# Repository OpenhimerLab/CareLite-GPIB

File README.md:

# CareLite-GPIB
CareLite is an open-source, tiny, small USB-GPIB adaptor based on STM32 with temperature sensors. 
It uses VCP (Virtual COM Port) and USB Type-C connector, without the need for external power; 
also with dedicated PC software (but not limited to), 
easy GPIB connection can be established and Prologix-like command protocol makes the compatiblity better, and real-time temp logging can be done by DS18B20 or so.

****I am NOT the author with no any relationship or benefit conflict with the author. I have no commercial intention to introdue this project and I have no intention to make benefits from this. 
All responsibility and risk or financial loss should be taken by the DIYers yourselves. The project is introduced and shared "AS IS".
Many functions, issues may exisit so use it at your own risk.

There are 2 version of MeterCare USB-GPIB converter, while sharing the same PC host Software, the firmware is unclear that both version could be applied.
We choose to introduce and share the "Lite" version firstly, as it is a simple, costless design somehow like AR488, 
but the designer reserves potentials to expand other functionality like temperature, humidity sensing ability (there is an UART+DS18B20 port, with proper firmware, it can be amazing for its various functionality!).

By the STM32F401, the CareLite can perform GPIB-USB conversion. 
In addition, there is a connector called MeterLink that provides the integration of multiple sensors(1 DS18B20 is confirmed to be functional).

Till now, at least 1 DS18B20 OneWire Temperature sensor can be used for logging temperature (by using MeterLink).

With the software written by "ZDD", you can connect a DMM and do a logging of both volt/ohm and temperature, and it will simutaneously calculate the math like temp.Co, or the deviation of logged data.
This makes it very clear to understand the dependency of multiple variables and its statistical property.

Also note that the software by ZDD is Labeview-based, you need to install:
1. NI Labview runtime
2. Local emulator to deal with encoding problems, as it is originally based on GBK simplified chinese, not UTF-8.

A sensor board with BMP180 and DS18B20, SHT2X is also possible for environment data logging, there is UART1 definition in MeterLink;
so it might be possible functional. This expansion board is mainly for the "Care" USB-GPIB, not sure if it is functional on CareLite.

The firmware is a bit messy, so try and find the best one for yourself. And explore the function, the Care ecosystem is very potential.
The protocol and communication is very like Prologix, using "++" command system, there are some explaination files, but it's in simplified Chinese,
for now I have no time to translate it, so please try by your own self. 
All in all, this is a tiny, easy to use GPIB adaptor for many devices, somthing like a STM32-based AR488 but with dedicated PC sotware!

For COPYright:

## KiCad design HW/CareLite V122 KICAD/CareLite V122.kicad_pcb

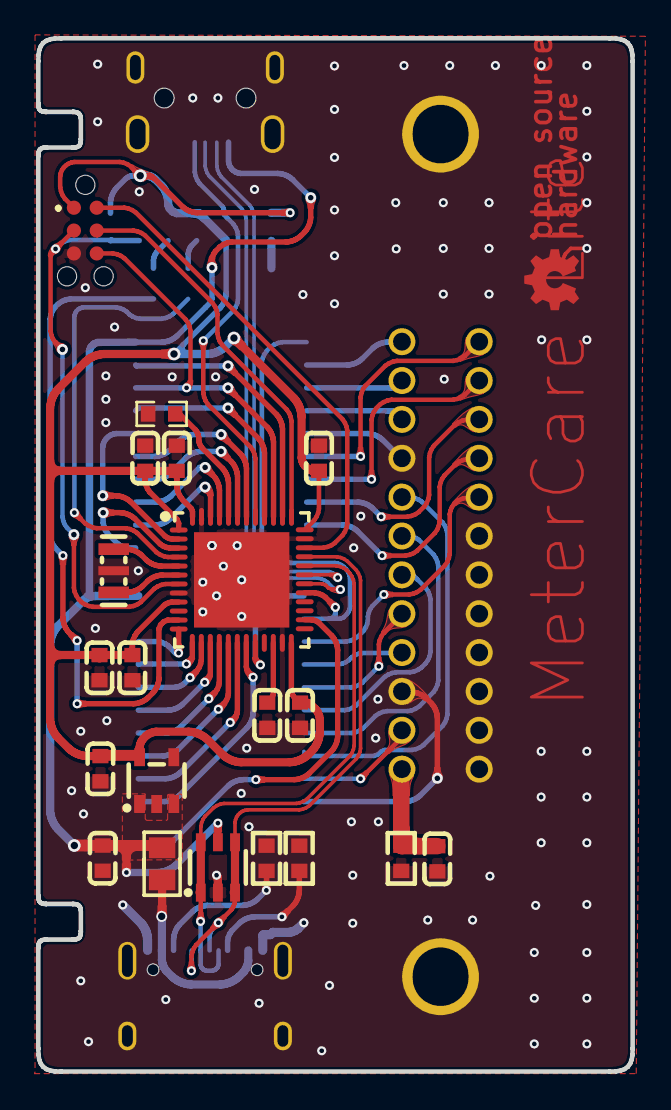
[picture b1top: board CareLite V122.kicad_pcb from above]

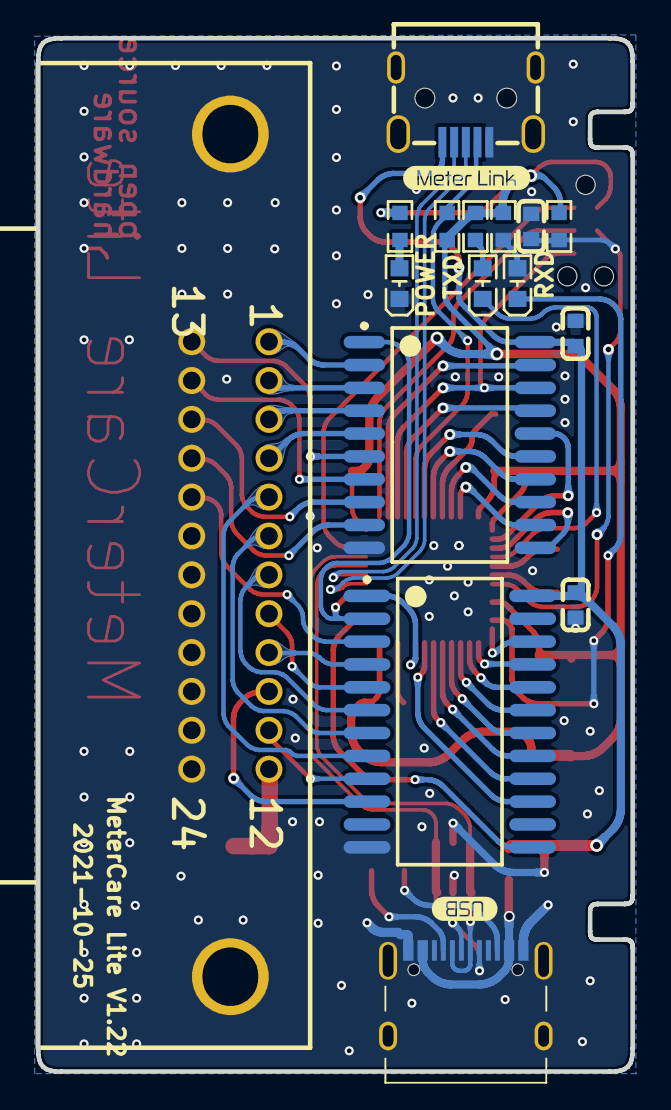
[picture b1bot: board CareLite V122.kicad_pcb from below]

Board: 2 copper layers, 33.0 x 57.4 mm, 37 parts (16 on the bottom side), 60 nets.

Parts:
C1, C12: 10uF; C0603
C2, C4, C6, C7, C8, C9, C10, C11: 100nF; C0603
C3: 4.7uF; C0603
C5: 1nF; C0603
C14: 100n; C0603
D1, D2, D3: LED; LED0603-FD
ESD: SRV05-4-P-T7; SOT-23-6_L2.9-W1.6-P0.95-LS2.8-BL
F1: 0.5A/6V; 0805_L_JX
GPIB: 112-024-113R001; IEEE-488 SOCKET, 24PIN, RIGHT ANGLE, MALE, 112-024-113R001,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
J1: 8.06.16; 80616-S
Pad_gge8544: Pad_gge8544
R1, R10: 5.1K; R0603
R2, R5, R6: 470R; R0603
R3, R9: 10K; R0603
R4: 1M; R0603
R7: 4.7K; R0603
U1: STM32F411CEU6TR; QFN-48_L7.0-W7.0-P0.50-BL-EP5.1
U2: LP5907QMFX-3.3Q1; SOT-23-5_L3.0-W1.7-P0.95-LS2.8-BR
U3: SN75160; SOIC127P1030-20AM
U5: SN75162; SOIC127P1030-24AM
USB: USB_C; USB_C_CUSB31-CFM2AX-01-Y
USB1: U-D-M7DS-G-2; MIRCO-USB-SMD_U-D-M7DS-G-2
X1: 8MHz; OSC-SMD_3P-L3.2-W1.3-P1.2-L

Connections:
ATN: GPIB.11, U5.9
CC1: R10.1, USB.A5
CC2: R1.1, USB.B5
D2_1: D2.1, R5.2
DAV: GPIB.6, U5.7
DIO1: GPIB.1, U3.2
DIO2: GPIB.2, U3.3
DIO3: GPIB.3, U3.4
DIO4: GPIB.4, U3.5
DIO5: GPIB.13, U3.6
DIO6: GPIB.14, U3.7
DIO7: GPIB.15, U3.8
DIO8: GPIB.16, U3.9
DS18B20: R7.2, U1.41, USB1.4
EOI: GPIB.5, U5.8
F1_1: F1.1, USB.A4B9, USB.B4A9
GND: C1.1, C2.2, C3.1, C4.2, C5.1, C6.1, C7.1, C8.1, C9.1, C10.1, C11.1, C12.1, C14.1, D3.2, ESD.2, GPIB.18, GPIB.19, GPIB.20, GPIB.21, GPIB.22, GPIB.23, GPIB.24, J1.5, R1.2, R3.2, R4.2, R10.2, U1.8, U1.23, U1.35, U1.47, U1.49, U2.2, U2.4, U3.10, U5.12, USB.A1B12, USB.B1A12, USB1.5, USB1.6, USB1.7, USB1.8, USB1.9, X1.2
GPIB_12: C5.2, GPIB.12, R4.1
IFC: GPIB.9, U5.4
IO_ATN: U1.18, U5.16
IO_DAV: U1.16, U5.18
IO_DC: U1.26, U5.13
IO_DIO1: U1.38, U3.19
IO_DIO2: J1.6, U1.39, U3.18
IO_DIO3: U1.40, U3.17
IO_DIO4: U1.2, U3.16
IO_DIO5: U1.42, U3.15
IO_DIO6: U1.43, U3.14
IO_DIO7: U1.45, U3.13
IO_DIO8: U1.46, U3.12
IO_EOI: U1.17, U5.17
IO_IFC: U1.13, U5.21
IO_NDAC: U1.14, U5.20
IO_NRFD: U1.15, U5.19
IO_PE: U1.3, U3.11
IO_REN: U1.12, U5.22
IO_SC: U1.20, U5.1
IO_SRQ: U1.19, U5.15
IO_TE: U1.29, U3.1, U5.2
LED1: D1.2, U1.11
LED2: D2.2, U1.4
NDAC: GPIB.8, U5.5
NRFD: GPIB.7, U5.6
NRST: C14.2, J1.3, R9.1, U1.7
OSC_IN: U1.5, X1.3
OSC_OUT: U1.6, X1.1
R2_2: D3.1, R2.2
R6_2: D1.1, R6.2
REN: GPIB.17, U5.3
SRQ: GPIB.10, U5.10
SWCLK: J1.4, U1.37
SWDIO: J1.2, U1.34
U1_22: C3.2, U1.22
U1_44: R3.1, U1.44
UART1_RX: U1.31, USB1.2
UART1_TX: U1.30, USB1.3
USB+: ESD.3, ESD.4, U1.33, USB.A6, USB.B6
USB-: ESD.1, ESD.6, U1.32, USB.A7, USB.B7
VCC: C6.2, C7.2, C8.2, C9.2, C10.2, C11.2, C12.2, J1.1, R2.1, R5.1, R6.1, R7.1, R9.2, U1.1, U1.9, U1.24, U1.36, U1.48, U2.5
VDD: C1.2, C2.1, C4.1, ESD.5, F1.2, U2.1, U2.3, U3.20, U5.24, USB1.1

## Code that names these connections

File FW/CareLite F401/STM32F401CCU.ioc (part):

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Mcu.Name=STM32F411C(C-E)Ux
Mcu.Package=UFQFPN48
Mcu.UserName=STM32F411CCUx
PA1.GPIOParameters=GPIO_Speed,PinState,GPIO_PuPd,GPIO_Label
PA1.GPIO_Label=LED1
PA1.GPIO_PuPd=GPIO_PULLUP
PA1.GPIO_Speed=GPIO_SPEED_FREQ_HIGH
PA1.PinState=GPIO_PIN_RESET
PA1.Signal=GPIO_Output
PA10.Mode=Asynchronous
PA10.Signal=USART1_RX
PA11.Mode=Device_Only
PA11.Signal=USB_OTG_FS_DM
PA12.Mode=Device_Only
PA12.Signal=USB_OTG_FS_DP
PA13.Mode=Serial_Wire
PA13.Signal=SYS_JTMS-SWDIO
PA14.Mode=Serial_Wire
PA14.Signal=SYS_JTCK-SWCLK
PA15.GPIOParameters=GPIO_Speed,PinState,GPIO_PuPd,GPIO_Label
PA15.GPIO_Label=DIO1
PA15.GPIO_PuPd=GPIO_PULLUP
PA15.GPIO_Speed=GPIO_SPEED_FREQ_HIGH
PA15.PinState=GPIO_PIN_SET
PA15.Signal=GPIO_Output
PA2.GPIOParameters=GPIO_Speed,PinState,GPIO_PuPd,GPIO_Label
PA2.GPIO_Label=REN
PA2.GPIO_PuPd=GPIO_PULLUP
PA2.GPIO_Speed=GPIO_SPEED_FREQ_HIGH
PA2.PinState=GPIO_PIN_SET
PA2.Signal=GPIO_Output
PA3.GPIOParameters=GPIO_Speed,PinState,GPIO_PuPd,GPIO_Label
PA3.GPIO_Label=IFC
PA3.GPIO_PuPd=GPIO_PULLUP
PA3.GPIO_Speed=GPIO_SPEED_FREQ_HIGH
PA3.PinState=GPIO_PIN_SET
PA3.Signal=GPIO_Output
PA4.GPIOParameters=GPIO_Speed,PinState,GPIO_PuPd,GPIO_Label
PA4.GPIO_Label=NDAC
PA4.GPIO_PuPd=GPIO_PULLUP
PA4.GPIO_Speed=GPIO_SPEED_FREQ_HIGH
PA4.PinState=GPIO_PIN_SET
PA4.Signal=GPIO_Output
PA5.GPIOParameters=GPIO_Speed,PinState,GPIO_PuPd,GPIO_Label
PA5.GPIO_Label=NRFD
PA5.GPIO_PuPd=GPIO_PULLUP
PA5.GPIO_Speed=GPIO_SPEED_FREQ_HIGH
PA5.PinState=GPIO_PIN_SET
PA5.Signal=GPIO_Output
PA6.GPIOParameters=GPIO_Speed,PinState,GPIO_PuPd,GPIO_Label
PA6.GPIO_Label=DAV
PA6.GPIO_PuPd=GPIO_PULLUP
PA6.GPIO_Speed=GPIO_SPEED_FREQ_HIGH
PA6.PinState=GPIO_PIN_SET
PA6.Signal=GPIO_Output
PA7.GPIOParameters=GPIO_Speed,PinState,GPIO_PuPd,GPIO_Label
PA7.GPIO_Label=EOI
PA7.GPIO_PuPd=GPIO_PULLUP
PA7.GPIO_Speed=GPIO_SPEED_FREQ_HIGH
PA7.PinState=GPIO_PIN_SET
PA7.Signal=GPIO_Output
PA8.GPIOParameters=GPIO_Speed,PinState,GPIO_PuPd,GPIO_Label
PA8.GPIO_Label=TE
PA8.GPIO_PuPd=GPIO_PULLUP
PA8.GPIO_Speed=GPIO_SPEED_FREQ_HIGH
PA8.PinState=GPIO_PIN_SET
PA8.Signal=GPIO_Output
PA9.Mode=Asynchronous
PA9.Signal=USART1_TX
PB0.GPIOParameters=GPIO_Speed,PinState,GPIO_PuPd,GPIO_Label
PB0.GPIO_Label=ATN
PB0.GPIO_PuPd=GPIO_PULLUP
PB0.GPIO_Speed=GPIO_SPEED_FREQ_HIGH
PB0.PinState=GPIO_PIN_SET
PB0.Signal=GPIO_Output
PB1.GPIOParameters=GPIO_Speed,PinState,GPIO_PuPd,GPIO_Label
PB1.GPIO_Label=SRQ
PB1.GPIO_PuPd=GPIO_PULLUP
PB1.GPIO_Speed=GPIO_SPEED_FREQ_HIGH
PB1.PinState=GPIO_PIN_SET
PB1.Signal=GPIO_Output
PB13.GPIOParameters=GPIO_Speed,PinState,GPIO_PuPd,GPIO_Label
PB13.GPIO_Label=DC
PB13.GPIO_PuPd=GPIO_PULLUP
PB13.GPIO_Speed=GPIO_SPEED_FREQ_HIGH
PB13.PinState=GPIO_PIN_SET
PB13.Signal=GPIO_Output
PB2.GPIOParameters=GPIO_Speed,PinState,GPIO_PuPd,GPIO_Label
PB2.GPIO_Label=SC
PB2.GPIO_PuPd=GPIO_PULLUP
PB2.GPIO_Speed=GPIO_SPEED_FREQ_HIGH
PB2.PinState=GPIO_PIN_SET
PB2.Signal=GPIO_Output
PB3.GPIOParameters=GPIO_Speed,PinState,GPIO_PuPd,GPIO_Label
PB3.GPIO_Label=DIO2
PB3.GPIO_PuPd=GPIO_PULLUP
PB3.GPIO_Speed=GPIO_SPEED_FREQ_HIGH
PB3.PinState=GPIO_PIN_SET
PB3.Signal=GPIO_Output
PB4.GPIOParameters=GPIO_Speed,PinState,GPIO_PuPd,GPIO_Label
PB4.GPIO_Label=DIO3
PB4.GPIO_PuPd=GPIO_PULLUP
PB4.GPIO_Speed=GPIO_SPEED_FREQ_HIGH
PB4.PinState=GPIO_PIN_SET
PB4.Signal=GPIO_Output
PB5.GPIOParameters=GPIO_Speed,PinState,GPIO_PuPd,GPIO_Label
PB5.GPIO_Label=DS18B20
PB5.GPIO_PuPd=GPIO_PULLUP
PB5.GPIO_Speed=GPIO_SPEED_FREQ_HIGH
PB5.PinState=GPIO_PIN_SET
PB5.Signal=GPIO_Output
PB6.GPIOParameters=GPIO_Speed,PinState,GPIO_PuPd,GPIO_Label
PB6.GPIO_Label=DIO5
PB6.GPIO_PuPd=GPIO_PULLUP
PB6.GPIO_Speed=GPIO_SPEED_FREQ_HIGH
PB6.PinState=GPIO_PIN_SET
PB6.Signal=GPIO_Output
PB7.GPIOParameters=GPIO_Speed,PinState,GPIO_PuPd,GPIO_Label
PB7.GPIO_Label=DIO6
PB7.GPIO_PuPd=GPIO_PULLUP
PB7.GPIO_Speed=GPIO_SPEED_FREQ_HIGH
PB7.PinState=GPIO_PIN_SET
PB7.Signal=GPIO_Output
PB8.GPIOParameters=GPIO_Speed,PinState,GPIO_PuPd,GPIO_Label
PB8.GPIO_Label=DIO7
PB8.GPIO_PuPd=GPIO_PULLUP
PB8.GPIO_Speed=GPIO_SPEED_FREQ_HIGH
PB8.PinState=GPIO_PIN_SET
PB8.Signal=GPIO_Output
PB9.GPIOParameters=GPIO_Speed,PinState,GPIO_PuPd,GPIO_Label
PB9.GPIO_Label=DIO8
PB9.GPIO_PuPd=GPIO_PULLUP
PB9.GPIO_Speed=GPIO_SPEED_FREQ_HIGH
PB9.PinState=GPIO_PIN_SET
PB9.Signal=GPIO_Output
PC13-ANTI_TAMP.GPIOParameters=PinState,GPIO_PuPd,GPIO_Label
PC13-ANTI_TAMP.GPIO_Label=DIO4
PC13-ANTI_TAMP.GPIO_PuPd=GPIO_PULLUP
PC13-ANTI_TAMP.PinState=GPIO_PIN_SET
PC13-ANTI_TAMP.Signal=GPIO_Output
PC14-OSC32_IN.GPIOParameters=PinState,GPIO_PuPd,GPIO_Label
PC14-OSC32_IN.GPIO_Label=PE
PC14-OSC32_IN.GPIO_PuPd=GPIO_PULLUP
PC14-OSC32_IN.PinState=GPIO_PIN_SET
PC14-OSC32_IN.Signal=GPIO_Output
PC15-OSC32_OUT.GPIOParameters=PinState,GPIO_PuPd,GPIO_Label
PC15-OSC32_OUT.GPIO_Label=LED2
PC15-OSC32_OUT.GPIO_PuPd=GPIO_PULLUP
PC15-OSC32_OUT.PinState=GPIO_PIN_RESET
PC15-OSC32_OUT.Signal=GPIO_Output
PH0\ -\ OSC_IN.Mode=HSE-External-Oscillator
PH0\ -\ OSC_IN.Signal=RCC_OSC_IN
PH1\ -\ OSC_OUT.Mode=HSE-External-Oscillator
PH1\ -\ OSC_OUT.Signal=RCC_OSC_OUT
RCC.HSE_VALUE=8000000
RCC.SYSCLKFreq_VALUE=72000000
RCC.SYSCLKSource=RCC_SYSCLKSOURCE_PLLCLK
board=custom

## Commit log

2024-06-24 Original Design Files
2024-06-27 Create CareLite RTX
2024-06-29 Add files via upload
    English GUI of DMM-PC TOOL
2024-06-29 Another Program for CareLite
